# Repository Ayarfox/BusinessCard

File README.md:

# PCB Business Card

A custom PCB card designed in KiCad, inspired by similar work done by [MarkWuElectronics](https://www.flux.ai/markwuflux).

## Features
- Custom PCB artwork and silkscreen
- NFC-tag with programmable functionality

I had these manufactured by JLCPCB for low cost and fast shipping.

## Files Included
- Schematic files and PCB files for KiCad
- Gerbers
- Images of the process

## License
This project is open-source and available under the MIT License.

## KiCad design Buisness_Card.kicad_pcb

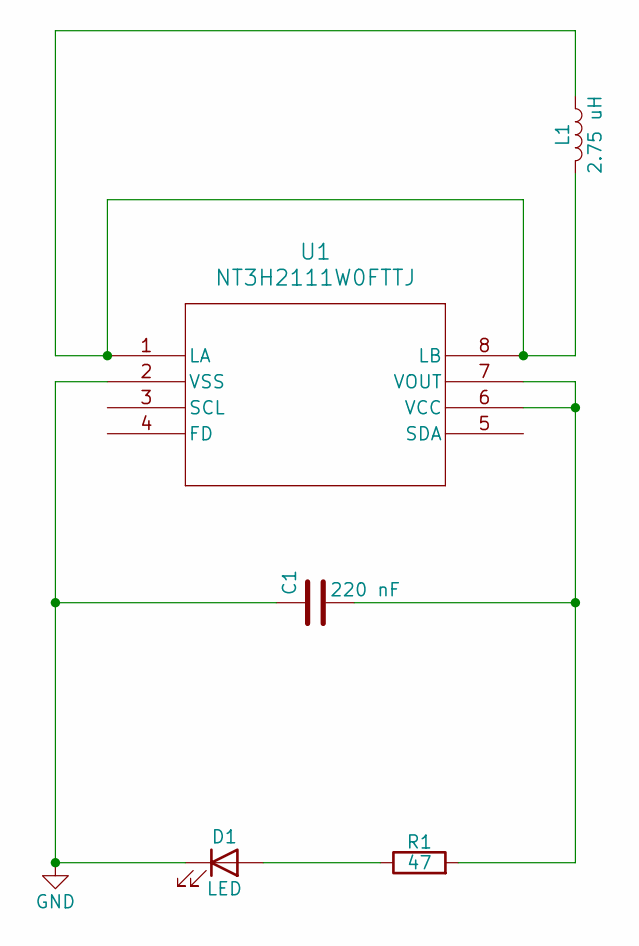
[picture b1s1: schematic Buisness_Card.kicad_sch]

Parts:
C1: 220 nF; C_0805_2012Metric_Pad1.18x1.45mm_HandSolder
D1: LED; LED_0805_2012Metric_Pad1.15x1.40mm_HandSolder
L1: 2.75 uH; RF_Induct
R1: 47; R_0402_1005Metric_Pad0.72x0.64mm_HandSolder
U1: NT3H2111W0FTTJ; TSSOP_1W0FTTJ_NXP-M

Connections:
unnamed: D1.2 (A), R1.1
unnamed: C1.1, D1.1 (K), U1.2 (VSS)
unnamed: L1.1, L1.2, U1.1 (LA), U1.8 (LB)
unnamed: C1.2, R1.2, U1.6 (VCC), U1.7 (VOUT)

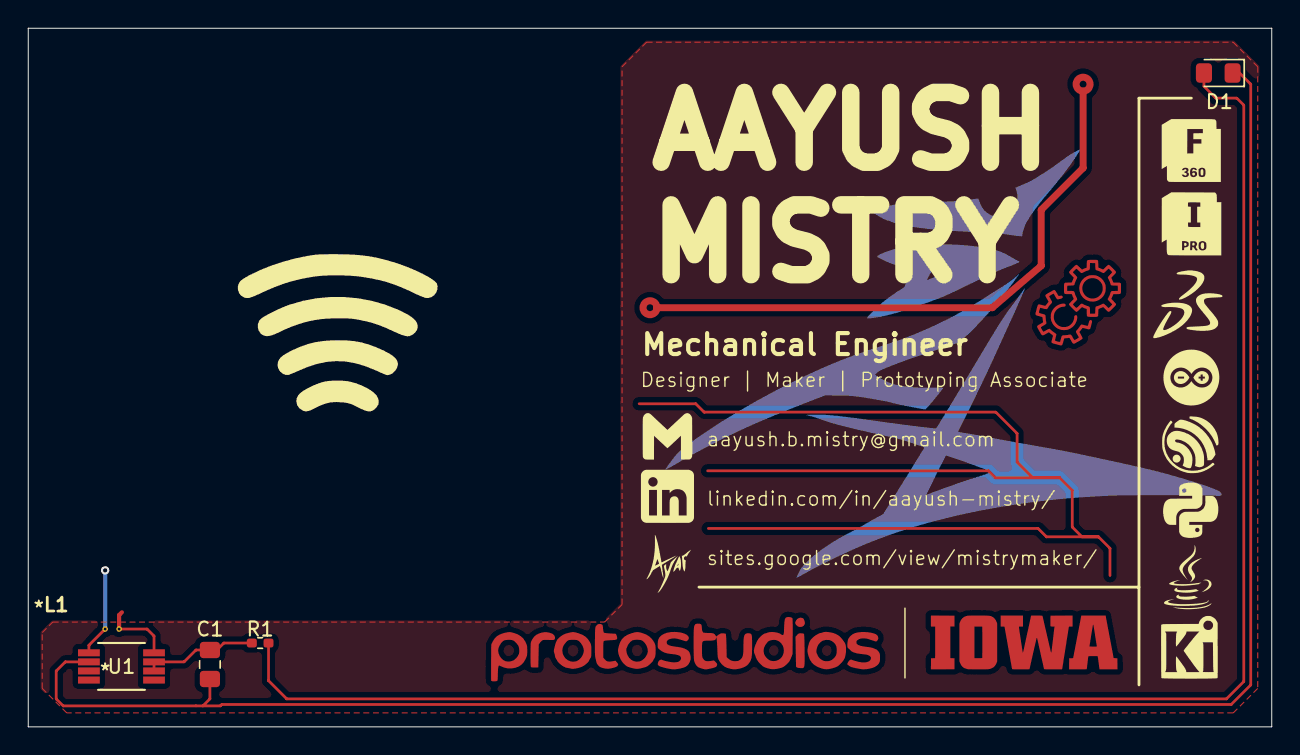
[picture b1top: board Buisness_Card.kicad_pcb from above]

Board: 2 copper layers, 89.0 x 50.0 mm, 5 parts (0 on the bottom side), 4 nets.

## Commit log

2026-05-27 Add placeholderhi to new file hi in GerberFiles
2026-05-27 Add files via upload
    All Gerbers
2026-05-27 Create hi
2026-05-27 Add files via upload
    Added Images
2026-05-27 Rename image_2026-05-26_231147807.png to Schematic
2026-05-27 Rename image_2026-05-26_231228406.png to Layout
2026-05-27 Rename image_2026-05-26_231248870.png to Render
2026-05-27 Create README.md for PCB Business Card project
    Added project details including features, images, and license information.
2026-05-27 Rename Schematic to Schematic.png
2026-05-27 Rename Render to Render.png
2026-05-27 Rename Layout to Layout.png
2026-05-27 Update README with PCB layout image and remove images section
    Removed project images section and added PCB layout image.
2026-05-27 Add MIT License to the project

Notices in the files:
Buisness_Card.kicad_sch:
Lisence: Creative Commons by 4.0
